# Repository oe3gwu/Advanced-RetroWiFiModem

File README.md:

# Advanced Retro WiFi Modem

> **AI-assisted advanced reimplementation** of the original [Retro WiFi Modem](https://github.com/oe3gwu/RetroWiFiModem).

An RS-232 WiFi modem with Hayes AT commands, status LEDs, and a full set of RS-232 control lines.

This repository offers **one Wemos PCB** (`kicad/wemos/`) and **two firmware variants** (pick the module, flash the matching firmware):

| Variant | Module | Uses `kicad/wemos/` | Firmware |
|---------|--------|---------------------|----------|
| **Wemos D1 Mini** | ESP8266 ([WEMOS D1 Mini](https://www.wemos.cc/en/latest/d1/index.html)) | Yes | `firmware/wemos-d1-mini/` |
| **Wemos C3 Mini** | ESP32-C3 ([WEMOS C3 Mini](https://www.wemos.cc/en/latest/c3/c3_mini.html)) | Yes (same board) | `firmware/wemos-c3-mini/` |

## Feature overview

| Feature | Wemos D1 Mini (ESP8266) | Wemos C3 Mini (ESP32-C3) | Maturity |
|---------|-------------------------|--------------------------|----------|
| Hayes AT, `ATDT`, Telnet, TCP server, NVRAM | ✓ | ✓ | Stable (core functionality) |
| OTA via Arduino IDE (developer) | ✓ | ✓ | Stable |
| **DFU** (`AT$DFU=…`) | ✓ | ✓ | **Experimental** — see below |
| **PPP + NAT** (`ATD*99#`) | ✗ (no stack / stub) | ✓ | ESP32-C3: tested with Linux `pppd`; C3 drop-in validated in field |
| **RAW / transparent mode** (`AT$MODE=RAW`) | ✓ | ✓ | Stable — see [RAW mode](#raw--transparent-mode) |
| **PCB (KiCad / Gerbers / BOM)** | ✓ | ✓ (same `kicad/wemos/`) | Wemos PCB: production-ready |

## What is in this repository

### Wemos PCB (for D1 mini and C3 Mini)

| Path | Contents |
|------|----------|
| `kicad/wemos/` | KiCad project, Gerbers, BOM — **one board for Wemos D1 Mini and Wemos C3 Mini** (Wemos-D1-mini socket; layout originally designed for ESP8266) |
| `firmware/wemos-d1-mini/Advanced-RetroWiFiModem/` | Firmware when a **D1 mini (ESP8266)** is installed |
| `firmware/wemos-c3-mini/Advanced-RetroWiFiModem/` | Firmware when a **C3 Mini (ESP32-C3)** is installed |

> **Order one PCB, pick your module:** `kicad/wemos/` is the same board for the Wemos D1 Mini and the Wemos C3 Mini — flash the matching firmware.

**Module choice**

| Module | Chip | On the Wemos PCB | Main limitation |
|--------|------|------------------|-----------------|
| **Wemos D1 Mini** | ESP8266 | Original design target | **No PPP** — Hayes/BBS/Telnet only |
| **Wemos C3 Mini** | ESP32-C3 | Drop-in, same socket | **PPP + NAT** plus everything the D1 mini does |

After swapping modules, flash the correct firmware and run **`AT&F`** once (EEPROM magic differs per platform).

**Why both modules fit mechanically and electrically**

The KiCad layout (`kicad/wemos/`) powers the module from the D1 mini header like this:

| D1 mini pad | Wemos PCB | Wemos C3 Mini | Notes |
|-------------|-----------|---------------|-------|
| **1** | **+5 V** | **VBUS / 5 V** | Module supply from the modem's 5 V rail |
| **2** | **GND** | **GND** | Common ground |
| **16** | 3.3 V | 3V3 | **Not connected** on the PCB (modem has its own 3.3 V regulator) |

So for this PCB only **5 V and GND** matter on the module header — and those match the C3 Mini pinout. No board rework required. Modem signal pins use the same **D-pin positions** on the shield; see [GPIO pinout comparison](#gpio-pinout-comparison).

**D1 mini notes**

- **Arduino IDE:** board package [esp8266 by ESP8266 Community](https://arduino.esp8266.com/stable/package_esp8266com_index.json) **3.2.2** (tested), board *LOLIN(WEMOS) D1 R2 & mini* — **not** *LOLIN(WEMOS) D1* (D1 R1); wrong board selection maps control lines to the wrong D-pins (e.g. DTR at D8 instead of D3). Earlier builds used core **2.7.x** — use **3.2.2** for current firmware.
- GPIO mapping in [GPIO pinout comparison](#gpio-pinout-comparison) applies only when compiled with **D1 R2 & mini**.

**C3 Mini notes**

- On the C3 Mini the **GPIO number printed at each header hole** is the one to use in firmware — same physical socket as the D1 mini D-pin, different GPIO.
- **GPIO7** (D3 / DTR socket) also drives the onboard RGB LED on v2.x.
- **GPIO8** (D2 / DSR socket) is an ESP32-C3 boot strap pin — fine as an output after boot; avoid pulling it low during reset.
- **Arduino IDE:** board package [esp32 by Espressif](https://docs.espressif.com/projects/arduino-esp32/) **3.x**, board *LOLIN C3 Mini*. PPP/NAT works with the stock lwIP build (no extra `build_opt.h` hacks).
- With default **USB CDC on boot**, RS-232 uses UART0 via `serial_port.h` (`Serial0` on GPIO20/21); USB remains available for upload/debug.

GPIO mapping for each firmware variant is in [GPIO pinout comparison](#gpio-pinout-comparison).

### General

| Path | Contents |
|------|----------|
| `LICENSE.txt` | GNU GPL v3 |

## Features

### Core (stable)

- RS-232 interface (DE-9) with TxD, RxD, RTS, CTS, DSR, DTR, DCD, and RI
- Hayes AT command set in WiFi232 style
- TCP connections to BBSes, Telnet servers, and other services
- Telnet protocol: real, fake (for certain BBSes), or disabled
- 10 speed-dial slots with alias names
- TCP server mode with optional password
- OTA firmware update over WiFi (Arduino IDE, developer workflow)

### New in this AI reimplementation

- **PPP dial-up with NAT (ESP32-C3 only):** `ATD*99#` or `AT$PPP=1` — retro host gets IP `192.168.240.2`, modem `192.168.240.1`, Internet access via WiFi NAT. Works on **Wemos C3 Mini**; not on ESP8266.
- **DFU (experimental, both platforms):** `AT$DFU=http://host/firmware.bin` or `AT$DFU=xmodem` — end-user update without the Arduino IDE; **at your own risk**, see [DFU](#dfu-firmware-update-via-at-command--experimental)

## Wemos PCB — hardware and assembly

**One PCB** in `kicad/wemos/` for **Wemos D1 Mini or Wemos C3 Mini** — plug either module into the same socket and flash the matching firmware. The layout was **originally designed for the [Wemos D1 Mini](https://docs.wemos.cc/en/latest/d1/d1_mini.html) (ESP8266)**; the C3 Mini uses the same Wemos-D1-mini footprint without board changes.

| Component | Function |
|-----------|----------|
| Wemos D1 Mini **or** Wemos C3 Mini | WiFi module (ESP8266 or ESP32-C3) |
| MAX3237 | RS-232 level shifter (3.3 V ↔ ±12 V) |
| 74HCT245 | LED drivers for status indicators |
| 74HC32 | OR gate — masks boot output on the serial line |
| LM2931 | Separate 3.3 V regulator for peripherals |
| DFPlayer Mini | Provided on the PCB (not driven by firmware) |

**Power:** 5 V, centre positive, 2.1 × 5.5 mm barrel jack.

**Order PCB:** Gerbers in `kicad/wemos/gerbers/`.

**Edit schematic:** open `kicad/wemos/RetroWiFiModem.kicad_pro` in KiCad.

### GPIO pinout comparison

Modem signals on the **Wemos PCB** use fixed **D-pin positions** on the Wemos D1 Mini header. The Wemos C3 Mini maps different GPIO numbers to those same positions (drop-in).

| Signal | D-pin | D1 mini GPIO | C3 Mini GPIO | Connection |
|--------|-------|--------------|--------------|------------|
| Serial TX | Tx | 1 | 21 | MAX3237 (via OR gate) |
| Serial RX | Rx | 3 | 20 | MAX3237 |
| DSR | D2 | 4 | 8 | MAX3237 |
| DCD | D1 | 5 | 10 | MAX3237 |
| DTR (input) | D3 | 0 | 7 | MAX3237 |
| TXEN | D5 | 14 | 1 | OR gate (mask boot garbage) |
| RI | D6 | 12 | 0 | MAX3237 + LED |
| RTS (input) | D7 | 13 | 4 | MAX3237 |
| CTS (output) | D8 | 15 | 5 | MAX3237 |

Firmware: `firmware/wemos-d1-mini/…/Advanced-RetroWiFiModem.h`, `firmware/wemos-c3-mini/…/Advanced-RetroWiFiModem.h`

> RTS/CTS are named from the modem (DCE) perspective.

## Firmware

Both variants share the same module structure:

| File | Function |
|------|----------|
| `Advanced-RetroWiFiModem.ino` | Main loop, setup |
| `Advanced-RetroWiFiModem.h` | Constants, pin definitions |
| `globals.h` | Global variables, settings structure |
| `support.h` | Helpers, Telnet, connection logic |
| `at_basic.h` | Standard AT commands |
| `at_extended.h` | Extended AT commands (&D, &F, &K, &W, …) |
| `at_proprietary.h` | Proprietary AT commands (AT$…) |
| `dfu.h` / `xmodem.h` | Experimental firmware update (AT$DFU) |
| `ppp.h` | PPP dial-up + NAT (ESP32-C3; ESP8266 stub) |

### Arduino IDE — board selection

Compile each sketch with the matching board in **Tools → Board**:

| Sketch path | Arduino board menu | Board package |
|-------------|-------------------|---------------|
| `firmware/wemos-d1-mini/` | **LOLIN(WEMOS) D1 R2 & mini** | esp8266 **3.2.2** |
| `firmware/wemos-c3-mini/` | **LOLIN C3 Mini** | esp32 **3.x** |

> **Do not use** *LOLIN(WEMOS) D1* (D1 **R1**) for the Wemos PCB — it selects a different GPIO map (DTR on D8 instead of D3). The RetroWiFiModem PCB is designed for the **D1 mini** form factor; always choose **D1 R2 & mini**.

### Wemos D1 Mini — `firmware/wemos-d1-mini/Advanced-RetroWiFiModem/`

For the Wemos PCB with **Wemos D1 Mini (ESP8266)** installed. In the Arduino IDE, open the sketch folder `Advanced-RetroWiFiModem.ino`.

**Arduino IDE — requirements:**

1. Board: *LOLIN(WEMOS) D1 R2 & mini*
2. ESP8266 core **3.2.2** (`https://arduino.esp8266.com/stable/package_esp8266com_index.json`) — upgrade from legacy **2.7.x** via Arduino IDE Board Manager (*esp8266 by ESP8266 Community*)
3. [ESP_EEPROM](https://github.com/jwrw/ESP_EEPROM) library, current version (2.2.0+)
4. `eeprom_storage.h` — lazy EEPROM init in `setup()` (no separate install needed)

The firmware initializes EEPROM in `setup()` with the correct flash sector (`EEPROM_start`). This makes `AT&W` work with ESP_EEPROM 2.2.x and ESP8266 core 3.2.2 — pinning to the older 2.1.2 ESP_EEPROM release or 2.7.x core is no longer required.

**Arduino IDE:** Tools → Flash Size must match your hardware (e.g. *4MB (FS:2MB OTA:~1019KB)*).

Select board and port, compile, and flash.

### Wemos C3 Mini — `firmware/wemos-c3-mini/Advanced-RetroWiFiModem/`

For the **same Wemos PCB** with **Wemos C3 Mini (ESP32-C3)** installed — see [Wemos PCB](#wemos-pcb-for-d1-mini-and-c3-mini) and [GPIO pinout comparison](#gpio-pinout-comparison).

**Arduino IDE — requirements:**

1. Install the [esp32 by Espressif](https://docs.espressif.com/projects/arduino-esp32/) board package **3.x** (PPP/NAT needs the current lwIP build)
2. Board: *LOLIN C3 Mini*
3. USB CDC On Boot: *Enabled* (default) — RS-232 still uses UART0 on GPIO20/21 via `serial_port.h`

Open the sketch folder in the Arduino IDE, compile, and flash. After swapping from a D1 mini, run **`AT&F`** once.

> EEPROM magic number: D1 mini `0x4321`, C3 Mini `0x4323` — settings are not interchangeable between platforms.

## Initial setup

Applies to both firmware variants. Factory default: **1200 baud, 8N1**. For initial setup, use `AT$SB=9600` followed by `AT&W`.

```
AT$SSID=MyWiFi
AT$PASS=MyPassword
ATC1
AT&W
```

Connect:

```
ATDTparticles                 ; speed dial by alias (factory default in &F)
ATDTaltair.virtualaltair.com  ; hostname
ATDT192.168.1.10:6400         ; IP with port
```

| Command | Description |
|---------|-------------|
| `AT$SB=n` | Baud rate (110 … 115200) |
| `AT$SU=dps` | Data bits, parity, stop bits (e.g. `8N1`) |
| `ATNETn` | Telnet: 0=off, 1=real, 2=fake |
| `AT&K1` | Hardware flow control (RTS/CTS) |
| `AT&Dn` | DTR behaviour: 0=ignore, 1=go offline, 2=hang up, 3=reset |
| `AT$SP=n` | TCP server port for incoming connections |
| `AT$MDNS=name` | mDNS name (default: `espmodem` / `esp32c3modem`) |
| `AT&Z0=host:port,alias` | Store speed dial |

Full help on device: `AT?`

## AT commands (quick reference)

Multiple commands per line are supported (`AT S0=1 Q0 V1`). String arguments (`AT$SSID=` etc.) must be at the end of the line.

**Connection:** `ATDT[+=-]host[:port]`, `ATDSn`, `ATA`, `ATH`, `ATO`, `+++` (escape)

**WiFi:** `ATC0`/`ATC1`, `ATI`, `ATGEThttp://…`, `ATRD`/`ATRT` (UTC via NTP, `pool.ntp.org`)

**Configuration:** `AT&W`, `AT&F`, `AT&V0`/`AT&V1`, `AT&Zn=…`, `AT$SSID=`, `AT$PASS=`, `AT$AE=`, `AT$BM=`, `AT&R=`, `ATZ`

**Behaviour:** `ATE0`/`ATE1`, `ATQ0`/`ATQ1`, `ATV0`/`ATV1`, `ATX0`/`ATX1`, `ATS0=n`, `ATS2=n`, `AT&D0`–`AT&D3`

**Experimental (AI reimplementation):** `AT$DFU=…` — details in [DFU](#dfu-firmware-update-via-at-command--experimental)

## DFU (firmware update via AT command) — **experimental**

> **Disclaimer / use at your own risk**  
> DFU is an **experimental** feature with no warranty. A wrong binary (wrong platform, corrupted file, interruption during flashing) can **brick** the device. Use only the **correct** `.bin` for **your** platform (ESP8266 or ESP32). Document a backup of settings (`AT&V1`) before updating. Recovery from a brick usually requires a **serial re-flash** over USB/UART (ESP8266: internal Wemos pins; ESP32: depends on your hardware). **The author accepts no liability** for damage from DFU use.

DFU does not replace proven **OTA via the Arduino IDE** (see [OTA updates](#ota-updates)). DFU targets end users without a development environment — with the risk noted above.

**Requirements:** command mode (not online), no active TCP session. HTTP DFU additionally requires WiFi connected (`ATC1`).

### HTTP DFU

```
AT$DFU=http://192.168.1.10/Advanced-RetroWiFiModem.ino.bin
```

The modem downloads the file over HTTP (no TLS), verifies it, and writes to the OTA partition. Progress on the serial console: `DOWNLOADING`, `VERIFYING`, `FLASHING`, `REBOOTING`.

```mermaid
sequenceDiagram
    participant User as Terminal
    participant Modem as Advanced-RetroWiFiModem
    participant HTTP as HTTP-Server
  User->>Modem: AT$DFU=http://host/fw.bin
  Note over Modem: WARNING: EXPERIMENTAL DFU
  Modem->>HTTP: GET /fw.bin
  HTTP-->>Modem: Firmware-Binary
  Modem-->>User: DOWNLOADING n%
  Modem-->>User: VERIFYING
  Modem-->>User: FLASHING
  Modem-->>User: REBOOTING
  Modem->>Modem: Reboot with new firmware
```

### XMODEM DFU (no HTTP server)

```
AT$DFU=xmodem
```

Then send the matching `.bin` file from your terminal program via XMODEM.

### Status

```
AT$DFU?
```

Possible responses: `idle`, `downloading`, `verifying`, `flashing`, `xmodem`, `error …`

## RAW / transparent mode

RAW mode is a **persistent** dataset-style operating mode for vintage hosts that expect a dumb modem (no Hayes commands on the serial line). DTR timing, RS-232 polarity, and host behaviour vary — test with **your** hardware.

RAW mode is stored in NVRAM (`AT$MODE=RAW` / `AT$MODE=AT`). After reboot the modem stays in the configured mode until changed again.

| | **AT mode** (default) | **RAW mode** |
|--|----------------------|--------------|
| Serial commands | Hayes `AT…` | None (byte pipe only) |
| Outbound dial | `ATDT…` | DTR asserted → Speed-Dial slot 0 |
| PPP | `ATD*99#` | Not available |
| Connect text | `CONNECT` / `NO CARRIER` | DCD only (no text) |
| Boot banner | WiFi status + `Mode: AT …` | WiFi status + `Mode: RAW …` |

### Setup (once, in AT mode)

```
AT&Z0=192.168.1.10:4000,myhost
AT$SB=110
AT$MODE=RAW
ATZ
```

Speed-Dial slot 0 defines the TCP target when the DTE asserts DTR. Recommended: 110 or 300 baud, `ATNET0` if you switch back to Hayes for BBS use.

### Return to AT mode (manual — not automatic)

1. Drop any active connection (release DTR).
2. Hold **DTR inactive for 5 seconds** — a **60 second maintenance window** opens and Hayes commands are accepted.
3. Type **`AT$MODE=AT`** — saved to NVRAM immediately.
4. **`ATZ`** — reboot into Hayes mode (recommended).

If step 3 is not completed within 60 seconds, the window closes and the modem **remains in RAW mode** (repeat the gesture).

### FAQ

**Does the modem switch to AT automatically after 5 seconds?**  
No. Five seconds of inactive DTR only opens the maintenance window. You must type `AT$MODE=AT` yourself.

**What if the 60 second window expires?**  
The modem stays in RAW mode. Repeat: disconnect, hold DTR inactive 5 s, then `AT$MODE=AT`.

## PPP (dial-up IP) — ESP32-C3

PPP turns the serial line into an IP link — for retro systems with `pppd`, Windows dial-up, or a native PPP stack. **Implemented on ESP32-C3** (lwIP `pppos` + NAT). On **ESP8266 (D1 mini)**, `ATD*99#` returns `NO CARRIER` (no PPP stack in the Arduino core). Use a **Wemos C3 Mini** on the same PCB for dial-up IP.

| Parameter | Value |
|-----------|-------|
| Modem IP (local) | `192.168.240.1` |
| Peer IP (retro host) | `192.168.240.2` |
| Authentication | PAP (empty user/password); CHAP only if present in lwIP build |
| Recommended baud rate | `AT$SB=57600` and `AT&W` before testing |

**Dial in:**

```
ATD*99#
```

or `AT$PPP=1` — then start `pppd` or Windows dial-up on the retro host.

**Hang up:** `ATH` or `AT$PPP=0`

`ATDT` (TCP) and PPP are mutually exclusive — only one online session at a time.

```mermaid
flowchart LR
  subgraph retro [Retro host]
    PPPD[pppd / DUN]
  end
  subgraph modem [ESP32 Modem]
    SER[RS-232]
    PPP[PPP stack]
    NAT[NAT]
    WIFI[WiFi STA]
  end
  subgraph lan [Internet]
    NET[Target host]
  end
  PPPD <-->|PPP frames| SER
  SER <--> PPP
  PPP <--> NAT
  NAT <--> WIFI
  WIFI --> NET
```

### Linux example (`pppd`)

Adjust serial port and baud rate. Important: `local nocrtscts` (no hardware handshake on the PC), otherwise DTR/GPIO0 can reset the ESP32.

**Manual dial** — dial on the modem first (`ATD*99#` or `AT$PPP=1`), then start `pppd`:

```bash
sudo pppd /dev/ttyUSB1 57600 local nocrtscts nodetach noauth \
  defaultroute replacedefaultroute usepeerdns \
  192.168.240.2:192.168.240.1
```

**Automatic dial** — `pppd` runs the Hayes chat script itself (no manual `ATD*99#`):

```bash
sudo pppd /dev/ttyUSB1 57600 local nocrtscts nodetach noauth \
  defaultroute replacedefaultroute usepeerdns \
  user "" password "" \
  192.168.240.2:192.168.240.1 \
  connect 'chat -v -t10 ABORT "NO CARRIER" ABORT "ERROR" "" "AT\r" "OK" "ATD*99#\r" "CONNECT"'
```

After `CONNECT` and successful IPCP:

```bash
ping 192.168.240.1          # modem
ping -I ppp0 8.8.8.8        # Internet via NAT (bring LAN interface down if needed)
```

> **Note:** If a default route over Ethernet already exists, `defaultroute` alone is often not enough — use `replacedefaultroute` or manually `ip route replace default dev ppp0`.

#### DNS (Linux / systemd-resolved)

`usepeerdns` accepts the DNS servers offered via IPCP (typically your WiFi router, e.g. `192.168.1.1`). On modern Linux with **systemd-resolved**, those servers often do not reach the active resolver — `ping 8.8.8.8` works but hostnames fail.

After the link is up, set DNS on the PPP interface (name is usually `ppp0`; check with `resolvectl status`):

```bash
sudo resolvectl dns ppp0 8.8.8.8 8.8.4.4
sudo resolvectl domain ppp0 '~.'
```

Then test:

```bash
ping www.google.at
```

**Still lightly tested:** Windows 9x/98 DUN, Amiga/DOS native PPP, TCP applications over NAT (mostly ICMP/ping so far), long-running operation.

## OTA updates

With an active WiFi connection: Arduino IDE → Sketch → Upload Using Network Address.

> After a firmware update with new EEPROM fields (e.g. `dtrHandling`), run `AT&W` or `AT&F` once so the NVRAM structure matches.

## Known limitations

- **Baud rate:** No auto-detection — `AT$SB` must match your terminal.
- **Linux Telnet / binary files:** Many `0xFF` bytes through `telnetd` can drop the connection (daemon issue, not the modem). Xmodem/Ymodem with 128-byte blocks as a workaround.
- **ESP8266 / RTS/CTS:** With `AT&K1` and long RTS idle, the watchdog may trigger. The firmware patches the UART send loop with `yield()`.
- **ESP8266 (D1 mini) / PPP:** Not available — `ATD*99#` returns `NO CARRIER`. Use **Wemos C3 Mini** on the same PCB for dial-up IP.
- **Wemos C3 Mini:** Drop-in on Wemos PCB; PPP/NAT with esp32 core 3.x.
- **DFU:** Experimental; wrong images can brick the device. No HTTPS. HTTP DFU requires WiFi; XMODEM does not.
- **PPP / ESP32-C3:** Primarily tested with Linux `pppd`; Windows DUN and CHAP still open.

## License

[GNU GPL v3](LICENSE.txt). Based on Virtual Modem code by Jussi Salin (2016), with extensions by Daniel Jameson, Stardot Contributors, and Paul Rickards (2018).

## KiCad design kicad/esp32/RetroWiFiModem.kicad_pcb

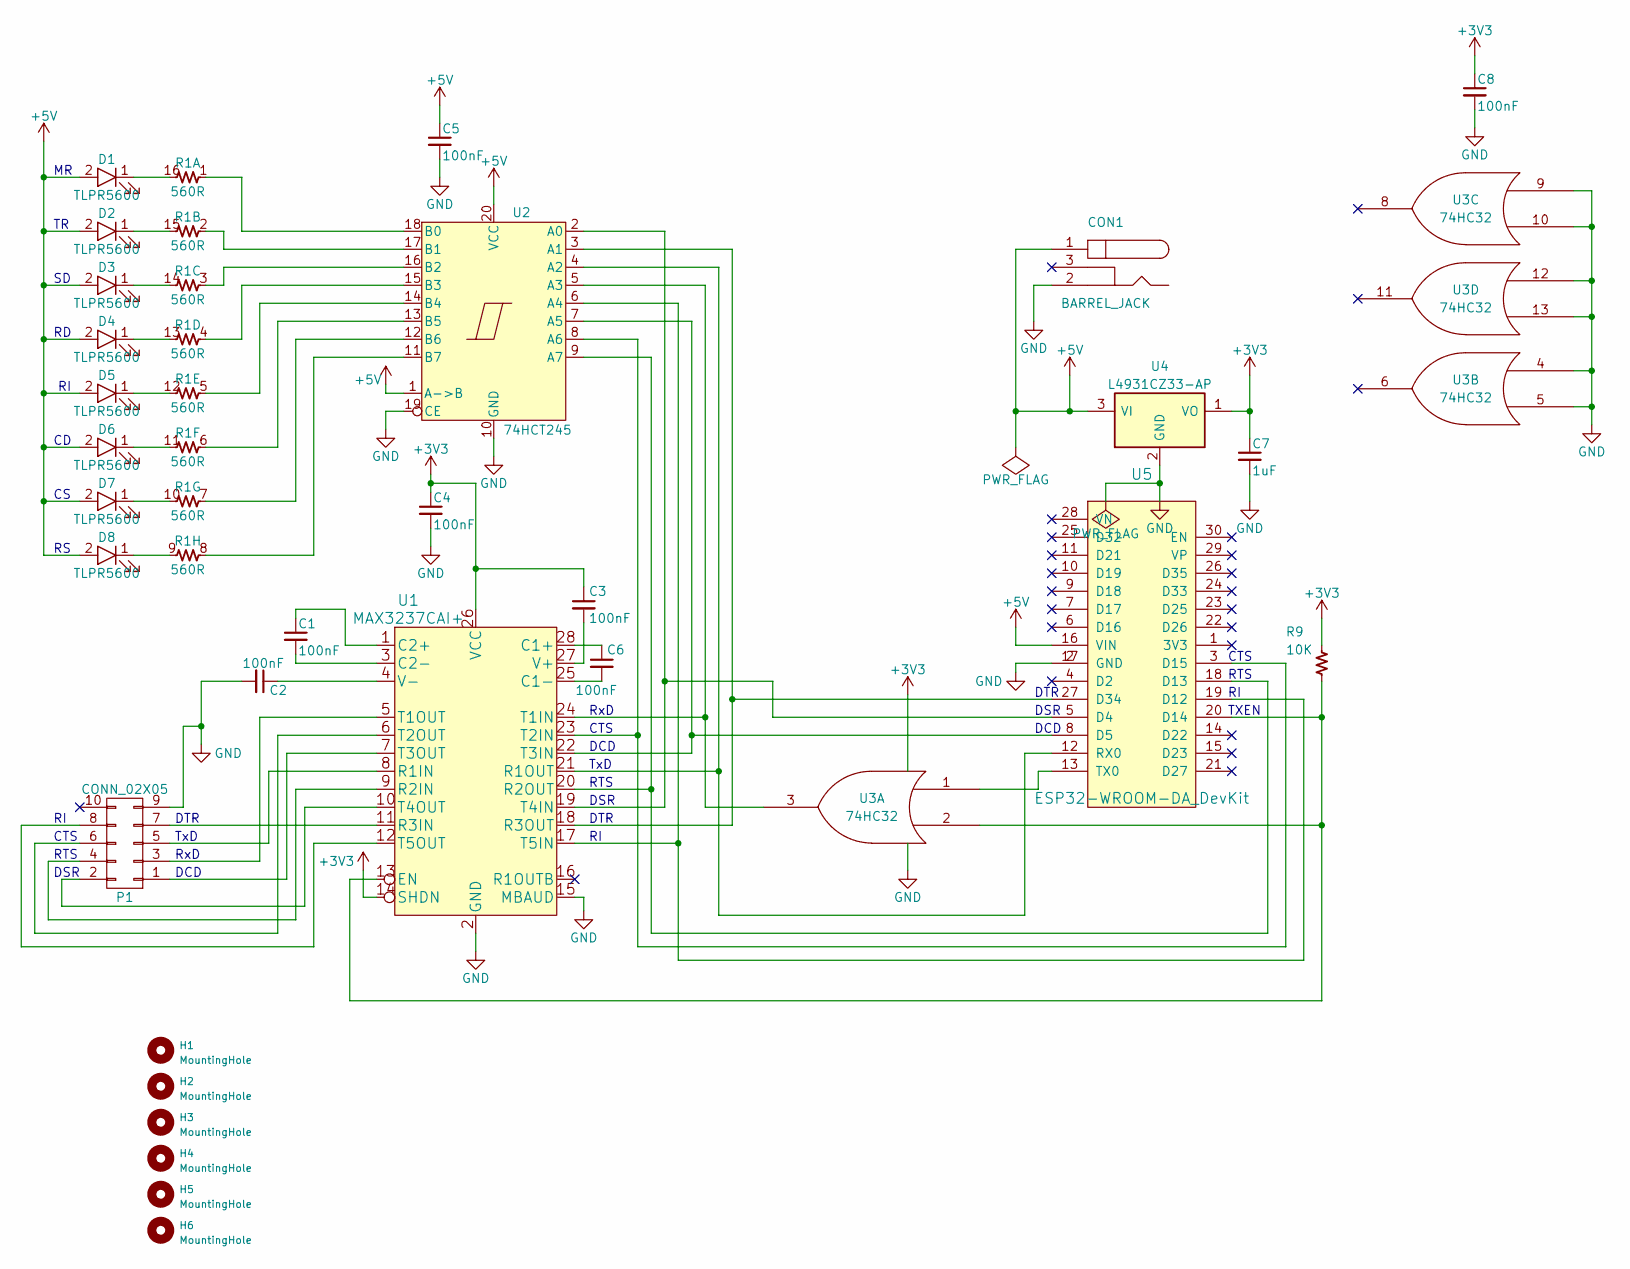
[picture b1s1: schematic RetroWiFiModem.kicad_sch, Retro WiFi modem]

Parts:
C1, C2, C3, C4, C5, C8: 100nF; C_Disc_D3_P2.5; DigiKey PN 399-9859-1-ND
C6: 100nF; R3; DigiKey PN 399-9843-ND
C7: 1uF; C_Disc_D3_P2.5; DigiKey PN 399-3529-ND
CON1: BARREL_JACK; BarrelJack_Horizontal; DigiKey PN 839-54-00166-ND
D1, D2, D3, D4, D5, D6, D7, D8: TLPR5600; LED-3MM; DigiKey PN TLPR5600-ND
H1, H2, H3, H4, H5, H6: MountingHole; MountingHole_3.2mm
P1: CONN_02X05; IDC_Header_Straight_10pins; DigiKey PN ED1543-ND
R1: 560R; DIP-16_W7.62mm_LongPads; DigiKey PN CF18JT560RCT-ND
R9: 10K; R3; DigiKey PN CF18JT10K0CT-ND
U1: MAX3237CAI+; SOIC-28W_7.5x17.9mm_Pitch1.27mm
U2: 74HCT245; SOIC-20W_7.5x12.8mm_P1.27mm
U3: 74HC32; SOIC-14_3.9x8.7mm_P1.27mm; DigiKey PN 296-1589-5-ND
U4: L4931CZ33-AP; TO-92_Inline_Wide; DigiKey PN LP2950ACZ-3.3GOS-ND
U5: ESP32-WROOM-DA_DevKit; ESP32-WROOM-DA-DevKit-30pin-USBC

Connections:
+3V3: C3.1, C4.1, C7.1, C8.1, R9.1, U1.14 (SHDN), U1.26 (VCC), U3.14 (VCC), U4.1 (VO)
+5V: C5.1, CON1.1, D1.2 (A), D2.2 (A), D3.2 (A), D4.2 (A), D5.2 (A), D6.2 (A), D7.2 (A), D8.2 (A), U2.1 (A->B), U2.20 (VCC), U4.3 (VI), U5.16 (VIN)
GND: C2.2, C4.2, C5.2, C7.2, C8.2, CON1.2, P1.9, U1.2 (GND), U1.15 (MBAUD), U2.10 (GND), U2.19 (CE), U3.4, U3.5, U3.7 (GND), U3.9, U3.10, U3.12, U3.13, U4.2 (GND), U5.2 (GND), U5.17 (GND)
unnamed: C1.1, U1.1 (C2+)
unnamed: C1.2, U1.3 (C2-)
unnamed: C2.1, U1.4 (V-)
unnamed: C3.2, U1.27 (V+)
unnamed: C6.1, U1.28 (C1+)
unnamed: C6.2, U1.25 (C1-)
unnamed: D1.1 (K), R1.16 (R1.2)
unnamed: D2.1 (K), R1.15 (R1.2)
unnamed: D3.1 (K), R1.14 (R1.2)
unnamed: D4.1 (K), R1.13 (R1.2)
unnamed: D5.1 (K), R1.12 (R1.2)
unnamed: D6.1 (K), R1.11 (R1.2)
unnamed: D7.1 (K), R1.10 (R1.2)
unnamed: D8.1 (K), R1.9 (R1.2)
unnamed: P1.1, U1.7 (T3OUT)
unnamed: P1.2, U1.10 (T4OUT)
unnamed: P1.3, U1.5 (T1OUT)
unnamed: P1.4, U1.9 (R2IN)
unnamed: P1.5, U1.8 (R1IN)
unnamed: P1.6, U1.6 (T2OUT)
unnamed: P1.7, U1.11 (R3IN)
unnamed: P1.8, U1.12 (T5OUT)
unnamed: R1.1 (R1.1), U2.18 (B0)
unnamed: R1.2 (R1.1), U2.17 (B1)
unnamed: R1.3 (R1.1), U2.16 (B2)
unnamed: R1.4 (R1.1), U2.15 (B3)
unnamed: R1.5 (R1.1), U2.14 (B4)
unnamed: R1.6 (R1.1), U2.13 (B5)
unnamed: R1.7 (R1.1), U2.12 (B6)
unnamed: R1.8 (R1.1), U2.11 (B7)
unnamed: R9.2, U1.13 (EN), U3.2, U5.20 (D14)
unnamed: U1.17 (T5IN), U2.6 (A4), U5.19 (D12)
unnamed: U1.18 (R3OUT), U2.3 (A1), U5.27 (D34)
unnamed: U1.19 (T4IN), U2.2 (A0), U5.5 (D4)
unnamed: U1.20 (R2OUT), U2.9 (A7), U5.18 (D13)
unnamed: U1.21 (R1OUT), U2.4 (A2), U5.12 (RX0)
unnamed: U1.22 (T3IN), U2.7 (A5), U5.8 (D5)
unnamed: U1.23 (T2IN), U2.8 (A6), U5.3 (D15)
unnamed: U1.24 (T1IN), U2.5 (A3), U3.3
unnamed: U3.1, U5.13 (TX0)

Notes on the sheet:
DCD
CTS
DSR
TxD
DTR
RxD
RTS
TXEN

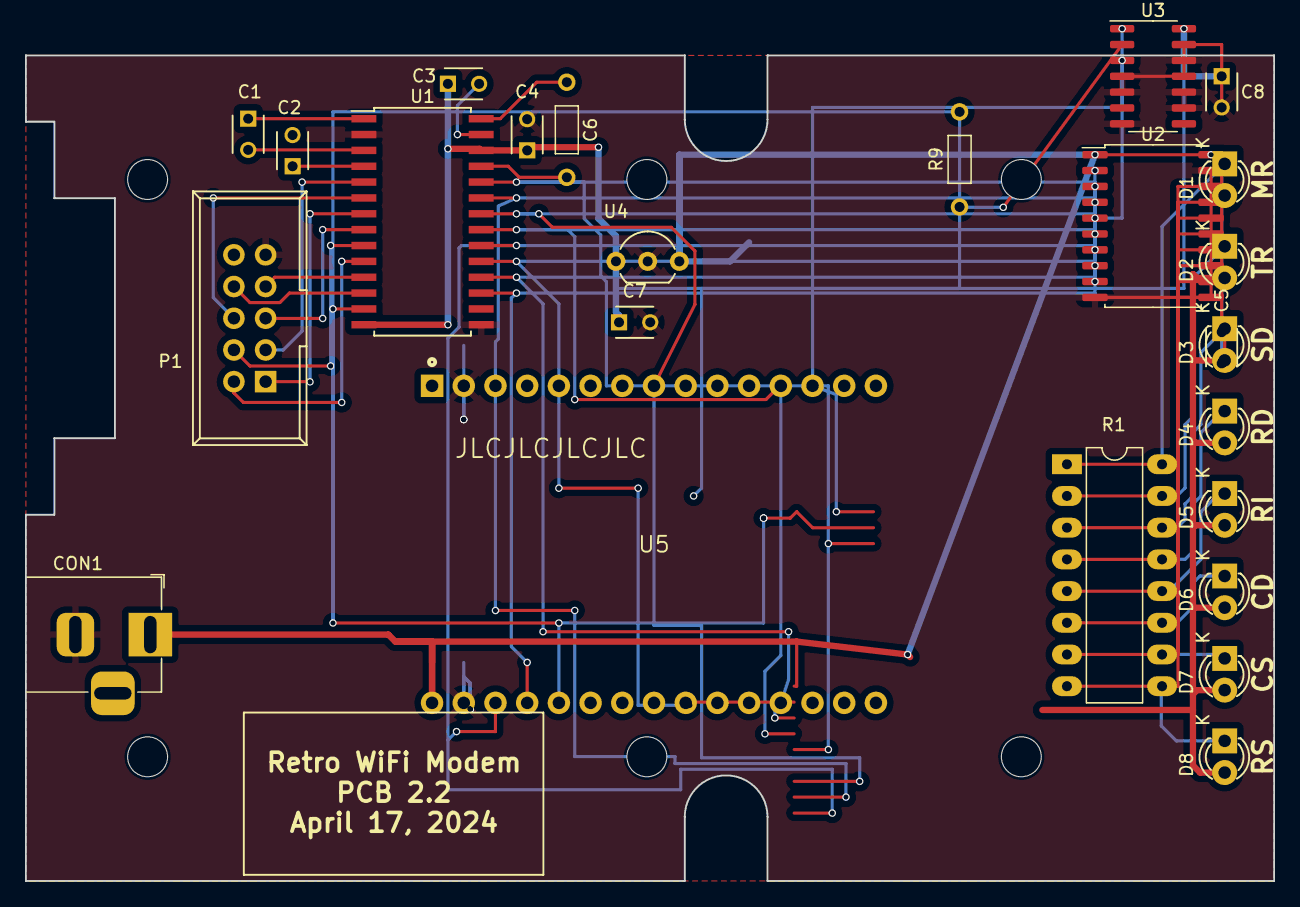
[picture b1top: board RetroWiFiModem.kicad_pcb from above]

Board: 2 copper layers, 100.0 x 66.1 mm, 31 parts (0 on the bottom side), 43 nets.

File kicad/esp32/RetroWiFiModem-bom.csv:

Reference,Quantity, Value, DigiKey PN,BC-Robotics PN
P1,1,CONN_02X05,ED1543-ND,
U3,1,SN74HC32DR,296-1199-1-ND,
U4,1,L4931CZ33-AP,LP2950ACZ-3.3GOS-ND,
D3-D8,8,TLPR5600,TLPR5600-ND,
"C1-C2,C4-C6,C8",6,100nF,399-9859-1-ND,
C7,1,1uF,399-3529-ND,
CON1,1,BARREL_JACK,839-54-00166-ND,
R1,8,560R,CF18JT560RCT-ND,
R9,1,10K,CF18JT10K0CT-ND,
U1,1,MAX3237ECDWR,296-36945-1-ND,
U2,1,74HCT245D,74HCT245DCT-ND,
C3,1,100nF,399-9859-1-ND,
U5,1,ESP32-WROOM-DA DevKit 30-pin USB-C,,
,1,Hammond 1593NBK case,HM963-ND ,
,1,Hammond red panel,HM889-ND ,
,50,PCB screws,HM1442-ND,
,1,5V wall adapter,364-1251-ND ,
,1,DE-9F IDC connector,5746861-4-ND,
,2,4-40 hex standoffs,A104867-ND,
,2,15 pos machine pin socket,2057-SMC-1-15-1-GT-ND,
,1,10 pos IDC socket,1175-1443-ND ,
,1,10 cond ribbon cable,3M157815-1-ND,
